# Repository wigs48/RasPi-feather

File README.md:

# RasPi-feather
RPi to Feather Adafruit Adapter Board

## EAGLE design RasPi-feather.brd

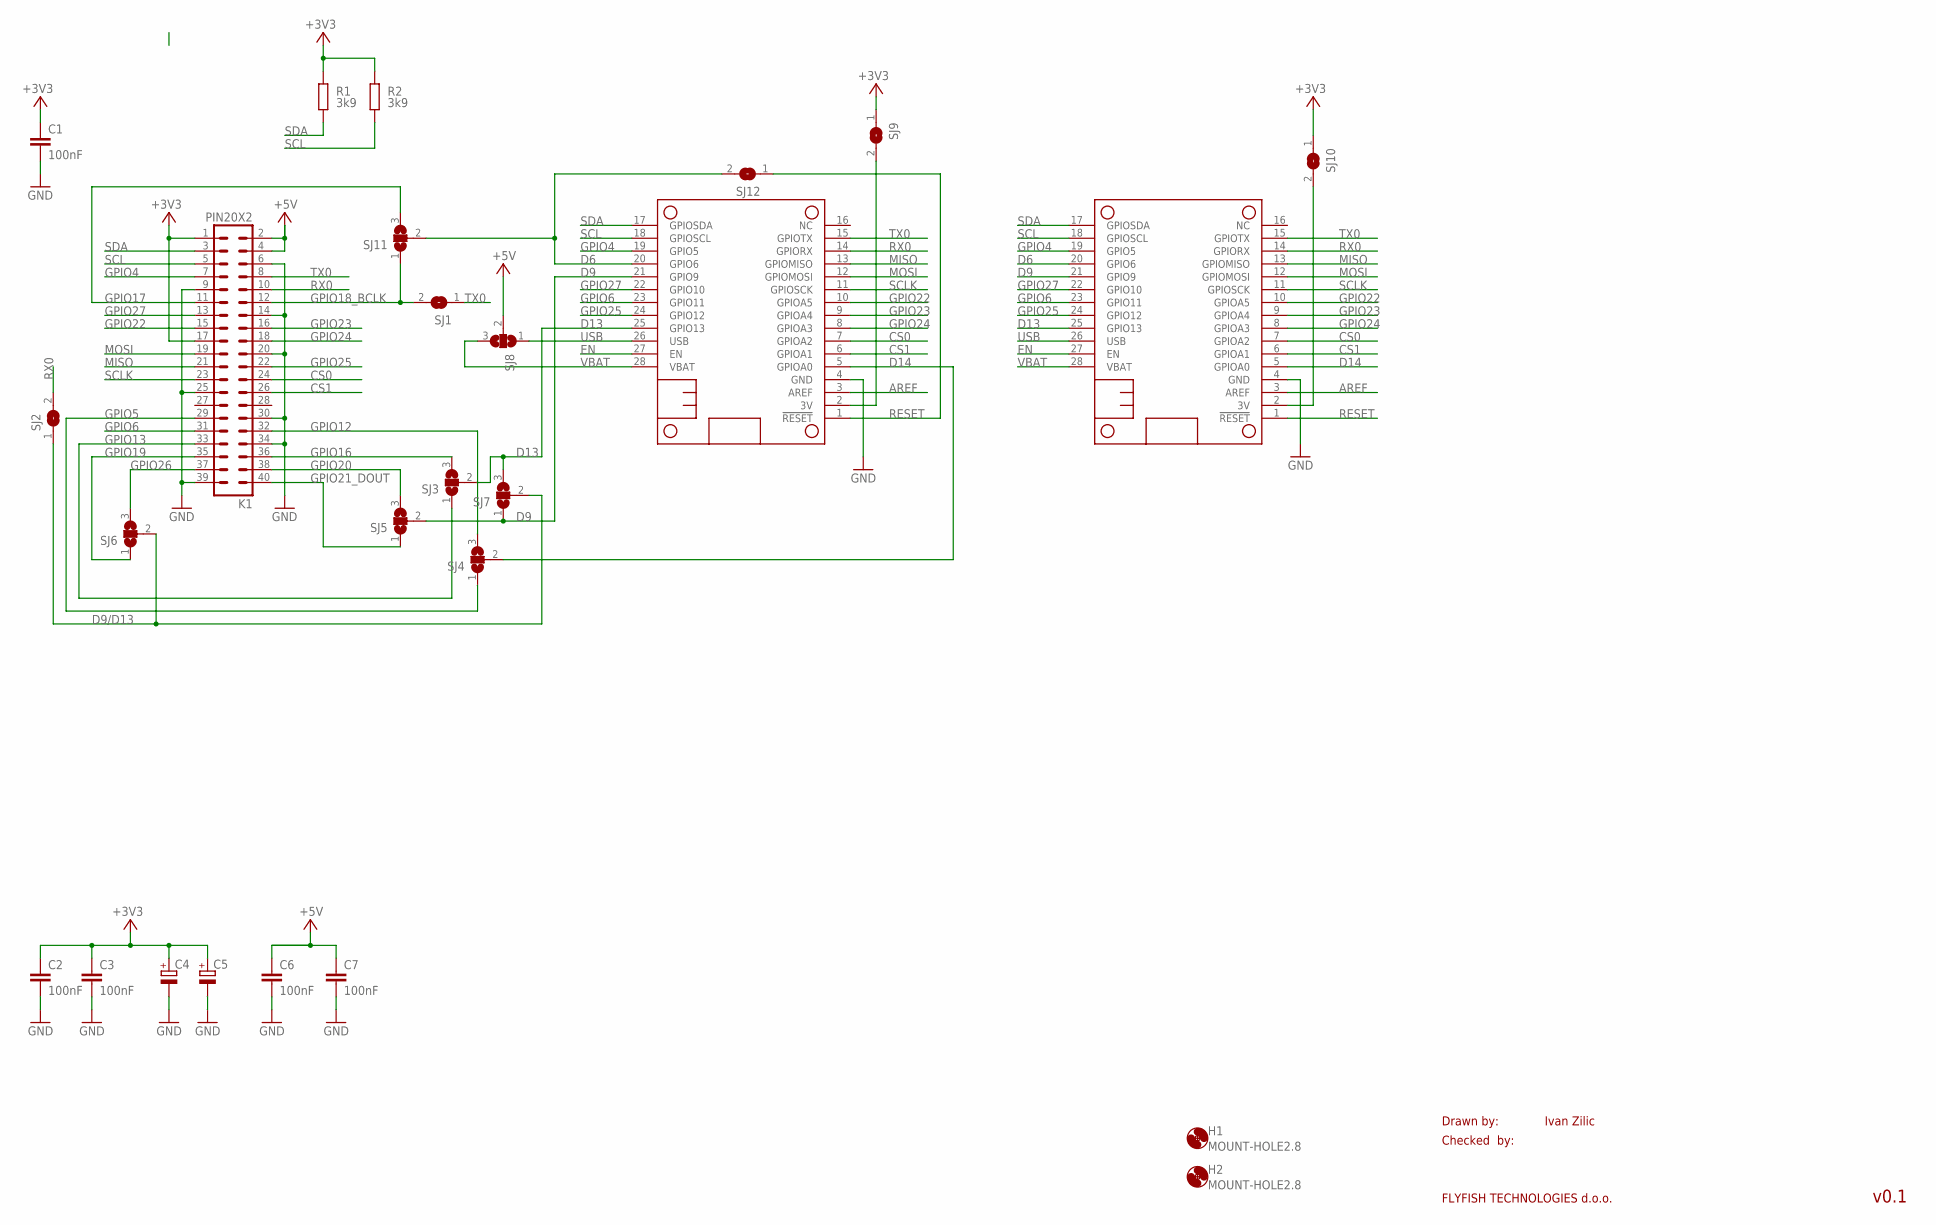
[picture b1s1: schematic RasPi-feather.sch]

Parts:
C1, C2, C3, C6, C7: 100nF; C0805K
C4, C5: CPOL-EUSMCD; SMC_D
H1, H2: MOUNT-HOLE2.8; 2,8
K1: PIN20X2; PIN_20X2
MS1, MS2: FEATHERWING_NODIM; FEATHERWING_DIM
R1, R2: 3k9; M0805; TOLERANCE 5%
SJ1, SJ2, SJ9, SJ10, SJ12: SJ
SJ3, SJ4, SJ5, SJ6, SJ7, SJ8, SJ11: SJ2W; SJ_2

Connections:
3V_1: MS1.2 (3V), SJ9.2
3V_2: MS2.2 (3V), SJ10.2
+3V3: C1.1, C2.1, C3.1, C4.+, C5.+, K1.1, K1.17, R1.2, R2.2, SJ9.1, SJ10.1
+5V: C6.1, C7.1, K1.2, K1.4, SJ8.2
AREF: MS1.3 (AREF), MS2.3 (AREF)
CS0: K1.24, MS1.7 (GPIOA2), MS2.7 (GPIOA2)
CS1: K1.26, MS1.6 (GPIOA1), MS2.6 (GPIOA1)
D6: MS1.20 (GPIO6), MS2.20 (GPIO6), SJ11.2, SJ12.2
D9: MS1.21 (GPIO9), MS2.21 (GPIO9), SJ5.2, SJ7.1
D9/D13: SJ2.1, SJ6.2, SJ7.2
D13: MS1.25 (GPIO13), MS2.25 (GPIO13), SJ3.2, SJ7.3
D14: MS1.5 (GPIOA0), MS2.5 (GPIOA0), SJ4.2
EN: MS1.27 (EN), MS2.27 (EN)
GND: C1.2, C2.2, C3.2, C4.-, C5.-, C6.2, C7.2, K1.6, K1.9, K1.14, K1.20, K1.25, K1.30, K1.34, K1.39, MS1.4 (GND), MS2.4 (GND)
GPIO4: K1.7, MS1.19 (GPIO5), MS2.19 (GPIO5)
GPIO5: K1.29, SJ4.1
GPIO6: K1.31, MS1.23 (GPIO11), MS2.23 (GPIO11)
GPIO12: K1.32, SJ4.3
GPIO13: K1.33, SJ3.1
GPIO16: K1.36, SJ3.3
GPIO17: K1.11, SJ11.3
GPIO18_BCLK: K1.12, SJ1.2, SJ11.1
GPIO19: K1.35, SJ6.1
GPIO20: K1.38, SJ5.3
GPIO21_DOUT: K1.40, SJ5.1
GPIO22: K1.15, MS1.10 (GPIOA5), MS2.10 (GPIOA5)
GPIO23: K1.16, MS1.9 (GPIOA4), MS2.9 (GPIOA4)
GPIO24: K1.18, MS1.8 (GPIOA3), MS2.8 (GPIOA3)
GPIO25: K1.22, MS1.24 (GPIO12), MS2.24 (GPIO12)
GPIO26: K1.37, SJ6.3
GPIO27: K1.13, MS1.22 (GPIO10), MS2.22 (GPIO10)
MISO: K1.21, MS1.13 (GPIOMISO), MS2.13 (GPIOMISO)
MOSI: K1.19, MS1.12 (GPIOMOSI), MS2.12 (GPIOMOSI)
RESET: MS1.1 (!RESET), MS2.1 (!RESET), SJ12.1
RX0: K1.10, MS1.14 (GPIORX), MS2.14 (GPIORX), SJ2.2
SCL: K1.5, MS1.18 (GPIOSCL), MS2.18 (GPIOSCL), R2.1
SCLK: K1.23, MS1.11 (GPIOSCK), MS2.11 (GPIOSCK)
SDA: K1.3, MS1.17 (GPIOSDA), MS2.17 (GPIOSDA), R1.1
TX0: K1.8, MS1.15 (GPIOTX), MS2.15 (GPIOTX), SJ1.1
USB: MS1.26 (USB), MS2.26 (USB), SJ8.1
VBAT: MS1.28 (VBAT), MS2.28 (VBAT), SJ8.3

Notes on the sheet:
Drawn by:
Checked by:
FLYFISH TECHNOLOGIES d.o.o.
Ivan Zilic
v0.1

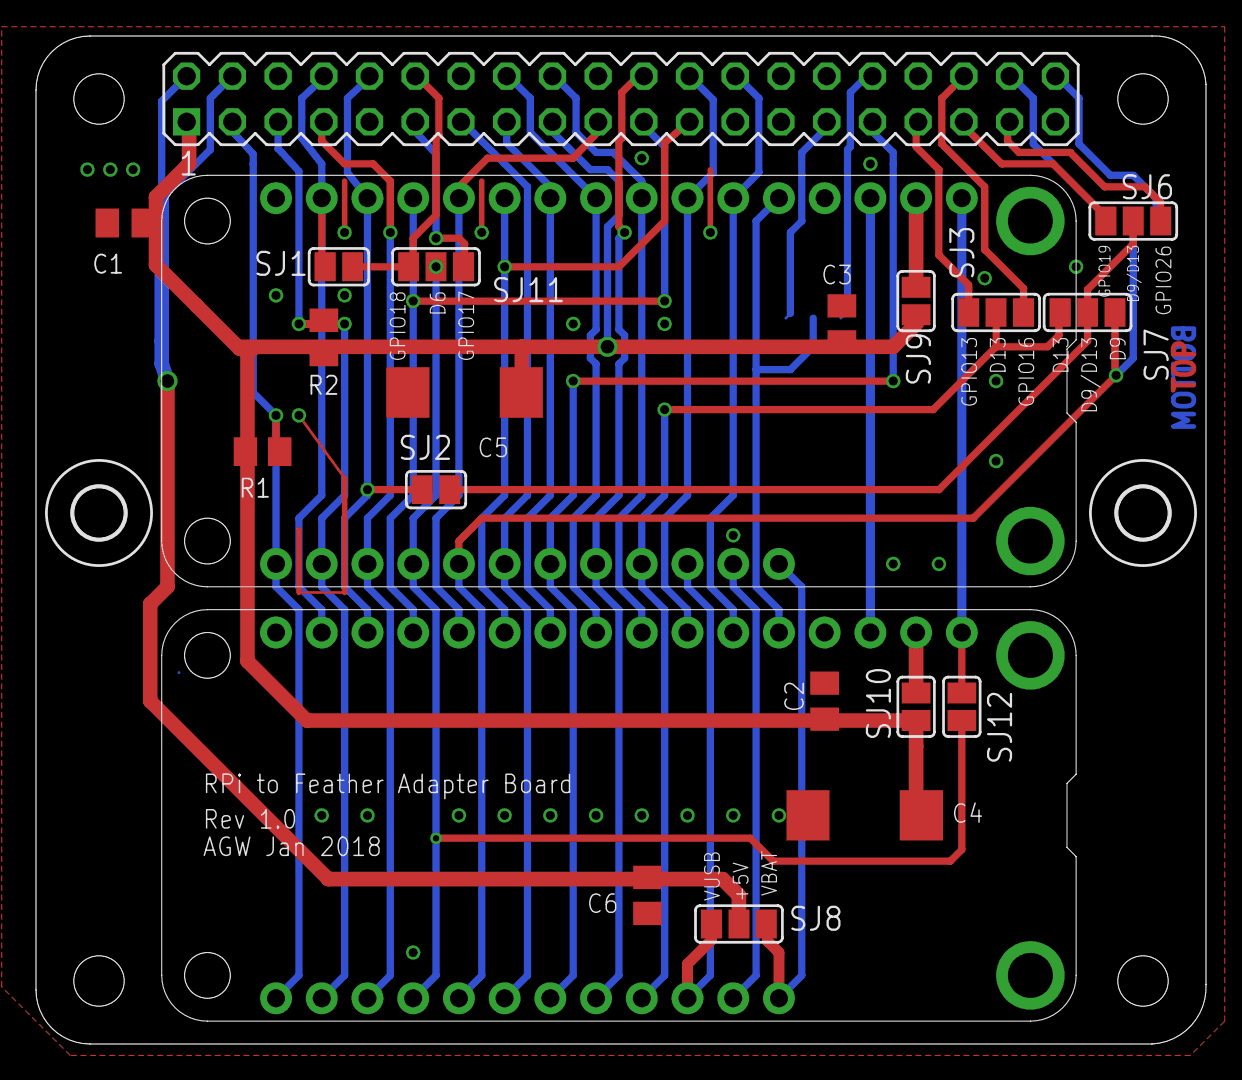
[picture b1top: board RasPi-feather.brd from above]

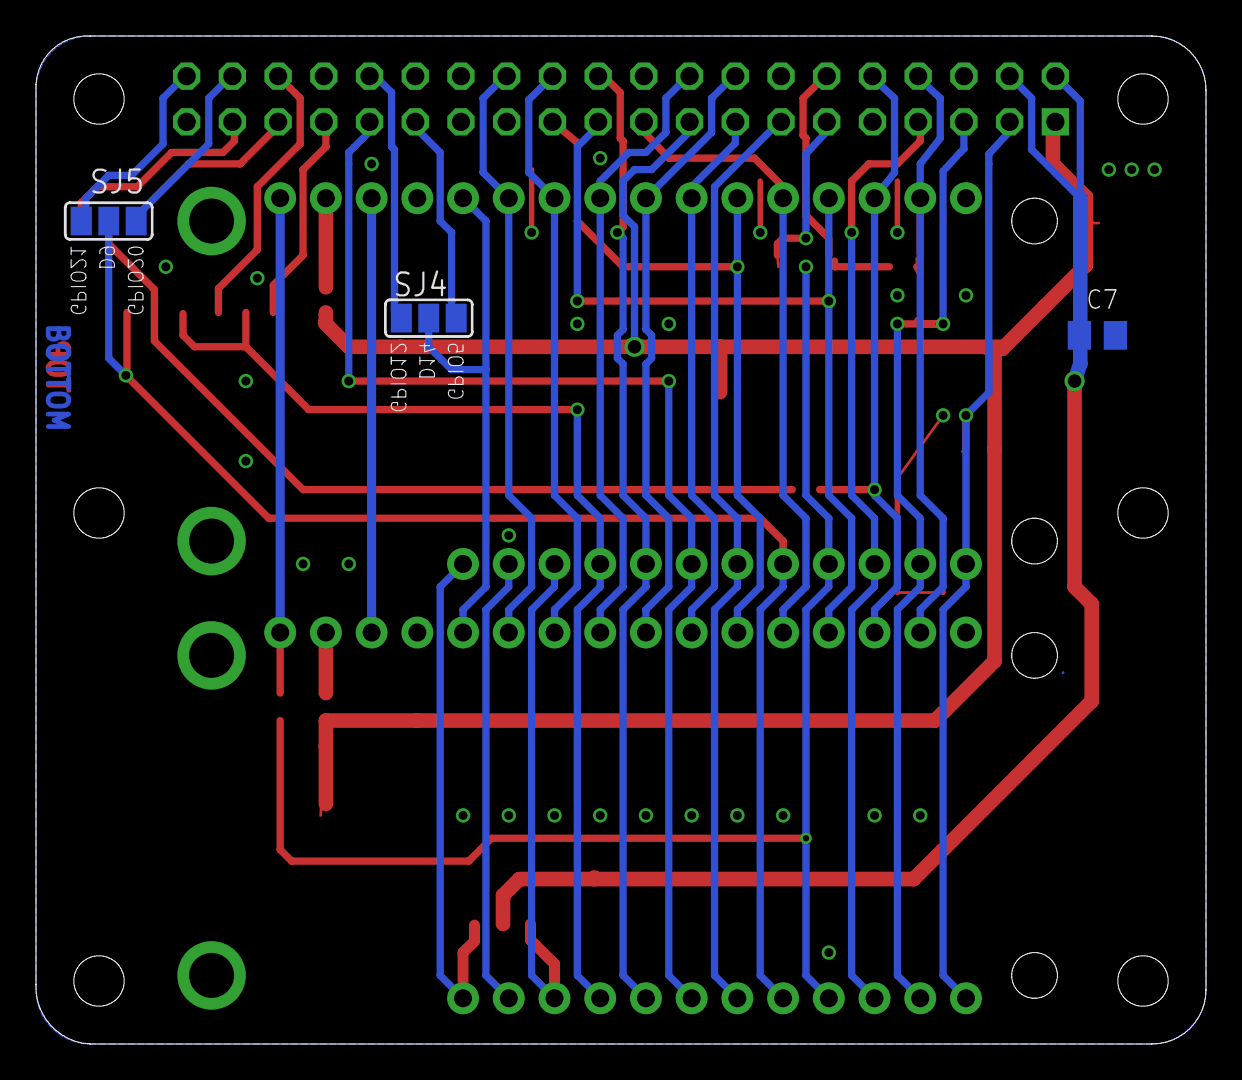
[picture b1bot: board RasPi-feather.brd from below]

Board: 2 copper layers, 65.0 x 56.0 mm, 26 parts (3 on the bottom side), 41 nets.
